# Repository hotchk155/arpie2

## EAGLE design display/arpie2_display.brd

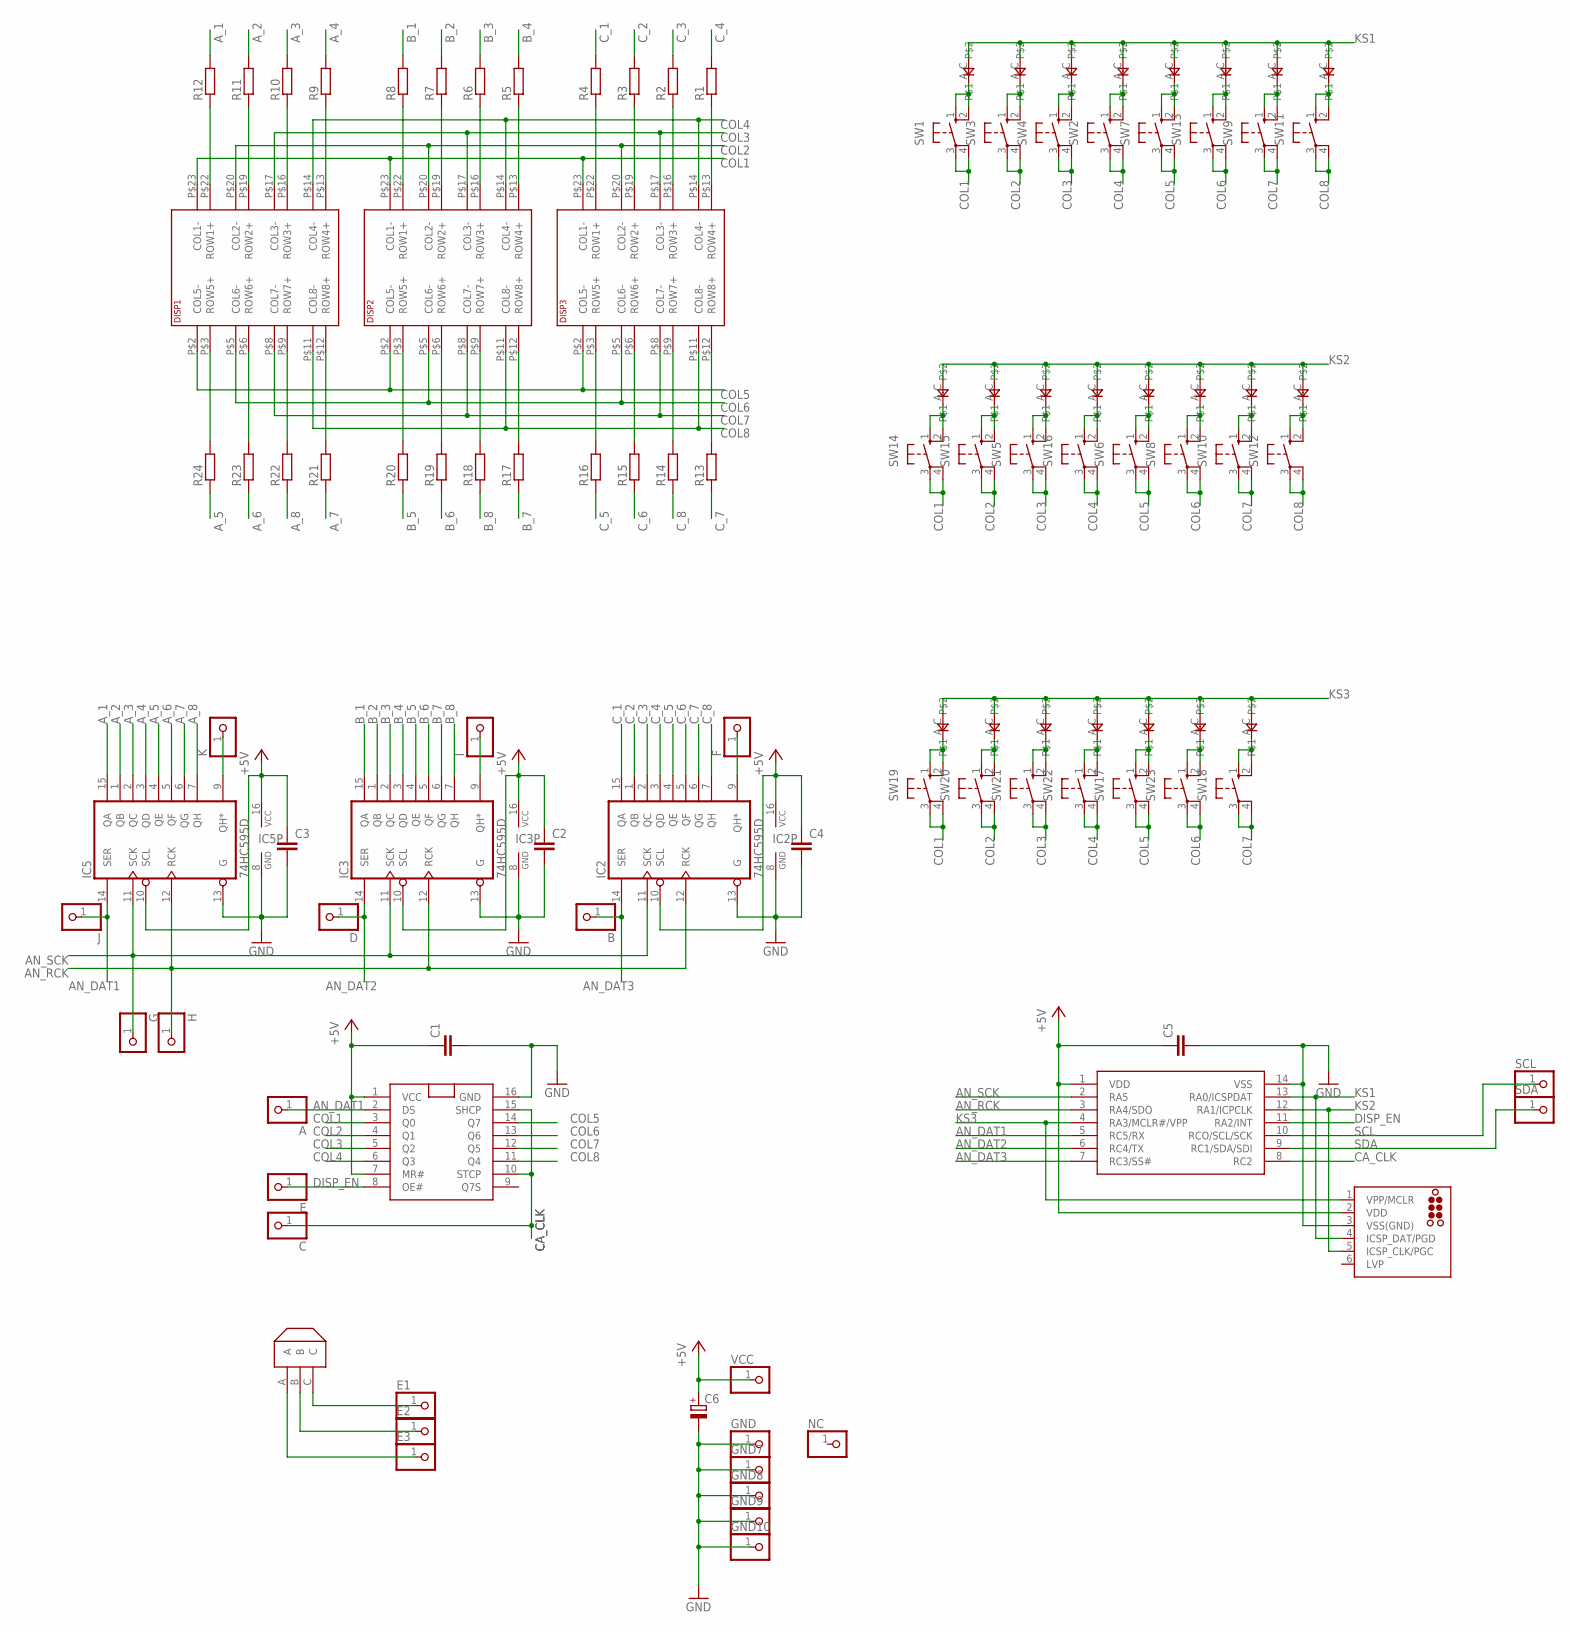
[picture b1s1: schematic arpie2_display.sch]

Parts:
A: PINHD-1X1; 1X01
B: PINHD-1X1; 1X01
C: PINHD-1X1; 1X01
C1, C2, C3, C4, C5: C-EUC0805; C0805
C6: CPOL-EUE2,5-6E; E2,5-6E
D: PINHD-1X1; 1X01
DISP1, DISP2, DISP3: 1388BBMATRIX; 1388LEDMATRIX
E, E1, E2, E3: PINHD-1X1; 1X01
ENC1: ENCODER
F: PINHD-1X1; 1X01
G: PINHD-1X1; 1X01
GND, GND7, GND8, GND9, GND10: PINHD-1X1; 1X01
H: PINHD-1X1; 1X01
I: PINHD-1X1; 1X01
IC1: PIC16F1825SO14; SO14
IC2, IC3, IC5: 74HC595D; SO16
IC4: NPIC6C596; SO16
ICSP: TC2030-MCP-NL
J: PINHD-1X1; 1X01
K: PINHD-1X1; 1X01
NC: PINHD-1X1; 1X01
R1, R2, R3, R4, R5, R6, R7, R8, R9, R10, R11, R12, R13, R14, R15, R16, R17, R18, R19, R20, R21, R22, R23, R24: R-EU_R0805; R0805
SCL: PINHD-1X1; 1X01
SDA: PINHD-1X1; 1X01
SW1, SW2, SW3, SW4, SW5, SW6, SW7, SW8, SW9, SW10, SW11, SW12, SW13, SW14, SW15, SW16, SW17, SW18, SW19, SW20, SW21, SW22, SW23: 10-XX; B3F-10XX
U$2, U$3, U$4, U$5, U$6, U$7, U$8, U$9, U$10, U$11, U$12, U$13, U$14, U$15, U$16, U$17, U$18, U$19, U$20, U$21, U$22, U$23, U$24: 0805DIODE
VCC: PINHD-1X1; 1X01

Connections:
+5V: C1.1, C2.1, C3.1, C4.1, C5.1, C6.+, IC1.1 (VDD), IC2.10 (SCL), IC2.16 (VCC), IC3.10 (SCL), IC3.16 (VCC), IC4.1 (VCC), IC4.7 (MR#), IC5.10 (SCL), IC5.16 (VCC), ICSP.2 (VDD), VCC.1
AN_DAT1: A.1, IC1.5 (RC5/RX), IC4.2 (DS), IC5.14 (SER), J.1
AN_DAT2: D.1, IC1.6 (RC4/TX), IC3.14 (SER)
AN_DAT3: B.1, IC1.7 (RC3/SS#), IC2.14 (SER)
AN_RCK: H.1, IC1.3 (RA4/SDO), IC2.12 (RCK), IC3.12 (RCK), IC5.12 (RCK)
AN_SCK: G.1, IC1.2 (RA5), IC2.11 (SCK), IC3.11 (SCK), IC5.11 (SCK)
A_1: IC5.15 (QA), R12.2
A_2: IC5.1 (QB), R11.2
A_3: IC5.2 (QC), R10.2
A_4: IC5.3 (QD), R9.2
A_5: IC5.4 (QE), R24.1
A_6: IC5.5 (QF), R23.1
A_7: IC5.6 (QG), R21.1
A_8: IC5.7 (QH), R22.1
B_1: IC3.15 (QA), R8.2
B_2: IC3.1 (QB), R7.2
B_3: IC3.2 (QC), R6.2
B_4: IC3.3 (QD), R5.2
B_5: IC3.4 (QE), R20.1
B_6: IC3.5 (QF), R19.1
B_7: IC3.6 (QG), R17.1
B_8: IC3.7 (QH), R18.1
CA_CLK: C.1, IC1.8 (RC2), IC4.10 (STCP), IC4.15 (SHCP)
COL1: DISP1.P$23 (COL1-), DISP2.P$23 (COL1-), DISP3.P$23 (COL1-), IC4.3 (Q0), SW1.3, SW1.4 (P1), SW14.3, SW14.4 (P1), SW19.3, SW19.4 (P1)
COL2: DISP1.P$20 (COL2-), DISP2.P$20 (COL2-), DISP3.P$20 (COL2-), IC4.4 (Q1), SW3.3, SW3.4 (P1), SW15.3, SW15.4 (P1), SW20.3, SW20.4 (P1)
COL3: DISP1.P$17 (COL3-), DISP2.P$17 (COL3-), DISP3.P$17 (COL3-), IC4.5 (Q2), SW4.3, SW4.4 (P1), SW5.3, SW5.4 (P1), SW21.3, SW21.4 (P1)
COL4: DISP1.P$14 (COL4-), DISP2.P$14 (COL4-), DISP3.P$14 (COL4-), IC4.6 (Q3), SW2.3, SW2.4 (P1), SW16.3, SW16.4 (P1), SW22.3, SW22.4 (P1)
COL5: DISP1.P$2 (COL5-), DISP2.P$2 (COL5-), DISP3.P$2 (COL5-), IC4.14 (Q7), SW6.3, SW6.4 (P1), SW7.3, SW7.4 (P1), SW17.3, SW17.4 (P1)
COL6: DISP1.P$5 (COL6-), DISP2.P$5 (COL6-), DISP3.P$5 (COL6-), IC4.13 (Q6), SW8.3, SW8.4 (P1), SW13.3, SW13.4 (P1), SW23.3, SW23.4 (P1)
COL7: DISP1.P$8 (COL7-), DISP2.P$8 (COL7-), DISP3.P$8 (COL7-), IC4.12 (Q5), SW9.3, SW9.4 (P1), SW10.3, SW10.4 (P1), SW18.3, SW18.4 (P1)
COL8: DISP1.P$11 (COL8-), DISP2.P$11 (COL8-), DISP3.P$11 (COL8-), IC4.11 (Q4), SW11.3, SW11.4 (P1), SW12.3, SW12.4 (P1)
C_1: IC2.15 (QA), R4.2
C_2: IC2.1 (QB), R3.2
C_3: IC2.2 (QC), R2.2
C_4: IC2.3 (QD), R1.2
C_5: IC2.4 (QE), R16.1
C_6: IC2.5 (QF), R15.1
C_7: IC2.6 (QG), R13.1
C_8: IC2.7 (QH), R14.1
DISP_EN: E.1, IC1.11 (RA2/INT), IC4.8 (OE#)
GND: C1.2, C2.2, C3.2, C4.2, C5.2, C6.-, GND.1, GND7.1, GND8.1, GND9.1, GND10.1, IC1.14 (VSS), IC2.8 (GND), IC2.13 (G), IC3.8 (GND), IC3.13 (G), IC4.16 (GND), IC5.8 (GND), IC5.13 (G), ICSP.3 (VSS(GND))
KS1: IC1.13 (RA0/ICSPDAT), ICSP.4 (ICSP_DAT/PGD), U$2.C, U$3.C, U$4.C, U$5.C, U$6.C, U$7.C, U$8.C, U$9.C
KS2: IC1.12 (RA1/ICPCLK), ICSP.5 (ICSP_CLK/PGC), U$10.C, U$11.C, U$12.C, U$13.C, U$14.C, U$15.C, U$16.C, U$17.C
KS3: IC1.4 (RA3/MCLR#/VPP), ICSP.1 (VPP/MCLR), U$18.C, U$19.C, U$20.C, U$21.C, U$22.C, U$23.C, U$24.C
unnamed: SW1.1 (S), SW1.2 (S1), U$2.A
unnamed: SW14.1 (S), SW14.2 (S1), U$10.A
unnamed: SW15.1 (S), SW15.2 (S1), U$11.A
unnamed: SW3.1 (S), SW3.2 (S1), U$3.A
unnamed: SW5.1 (S), SW5.2 (S1), U$12.A
unnamed: SW16.1 (S), SW16.2 (S1), U$13.A
unnamed: SW4.1 (S), SW4.2 (S1), U$4.A
unnamed: SW6.1 (S), SW6.2 (S1), U$14.A
unnamed: DISP1.P$22 (ROW1+), R12.1
unnamed: DISP1.P$19 (ROW2+), R11.1
unnamed: DISP1.P$16 (ROW3+), R10.1
unnamed: DISP1.P$13 (ROW4+), R9.1
unnamed: DISP2.P$22 (ROW1+), R8.1
unnamed: DISP2.P$19 (ROW2+), R7.1
unnamed: DISP2.P$16 (ROW3+), R6.1
unnamed: DISP2.P$13 (ROW4+), R5.1
unnamed: DISP3.P$22 (ROW1+), R4.1
unnamed: DISP3.P$19 (ROW2+), R3.1
unnamed: DISP3.P$16 (ROW3+), R2.1
unnamed: DISP3.P$13 (ROW4+), R1.1
unnamed: DISP1.P$3 (ROW5+), R24.2
unnamed: DISP1.P$6 (ROW6+), R23.2
unnamed: DISP1.P$9 (ROW7+), R22.2
unnamed: DISP1.P$12 (ROW8+), R21.2
unnamed: DISP2.P$3 (ROW5+), R20.2
unnamed: DISP2.P$6 (ROW6+), R19.2
unnamed: DISP2.P$9 (ROW7+), R18.2
unnamed: DISP2.P$12 (ROW8+), R17.2
unnamed: DISP3.P$3 (ROW5+), R16.2
unnamed: DISP3.P$6 (ROW6+), R15.2
unnamed: DISP3.P$9 (ROW7+), R14.2
unnamed: DISP3.P$12 (ROW8+), R13.2
unnamed: SW8.1 (S), SW8.2 (S1), U$15.A
unnamed: SW2.1 (S), SW2.2 (S1), U$5.A
unnamed: SW10.1 (S), SW10.2 (S1), U$16.A
unnamed: SW12.1 (S), SW12.2 (S1), U$17.A
unnamed: SW7.1 (S), SW7.2 (S1), U$6.A
unnamed: SW19.1 (S), SW19.2 (S1), U$18.A
unnamed: SW20.1 (S), SW20.2 (S1), U$19.A
unnamed: SW13.1 (S), SW13.2 (S1), U$7.A
unnamed: SW21.1 (S), SW21.2 (S1), U$20.A
unnamed: SW22.1 (S), SW22.2 (S1), U$21.A
unnamed: SW9.1 (S), SW9.2 (S1), U$8.A
unnamed: SW17.1 (S), SW17.2 (S1), U$22.A
unnamed: SW23.1 (S), SW23.2 (S1), U$23.A
unnamed: SW11.1 (S), SW11.2 (S1), U$9.A
unnamed: SW18.1 (S), SW18.2 (S1), U$24.A
unnamed: E1.1, ENC1.C
unnamed: E2.1, ENC1.B
unnamed: E3.1, ENC1.A
unnamed: IC5.9 (QH*), K.1
unnamed: I.1, IC3.9 (QH*)
unnamed: F.1, IC2.9 (QH*)
SCL: IC1.10 (RCO/SCL/SCK), SCL.1
SDA: IC1.9 (RC1/SDA/SDI), SDA.1

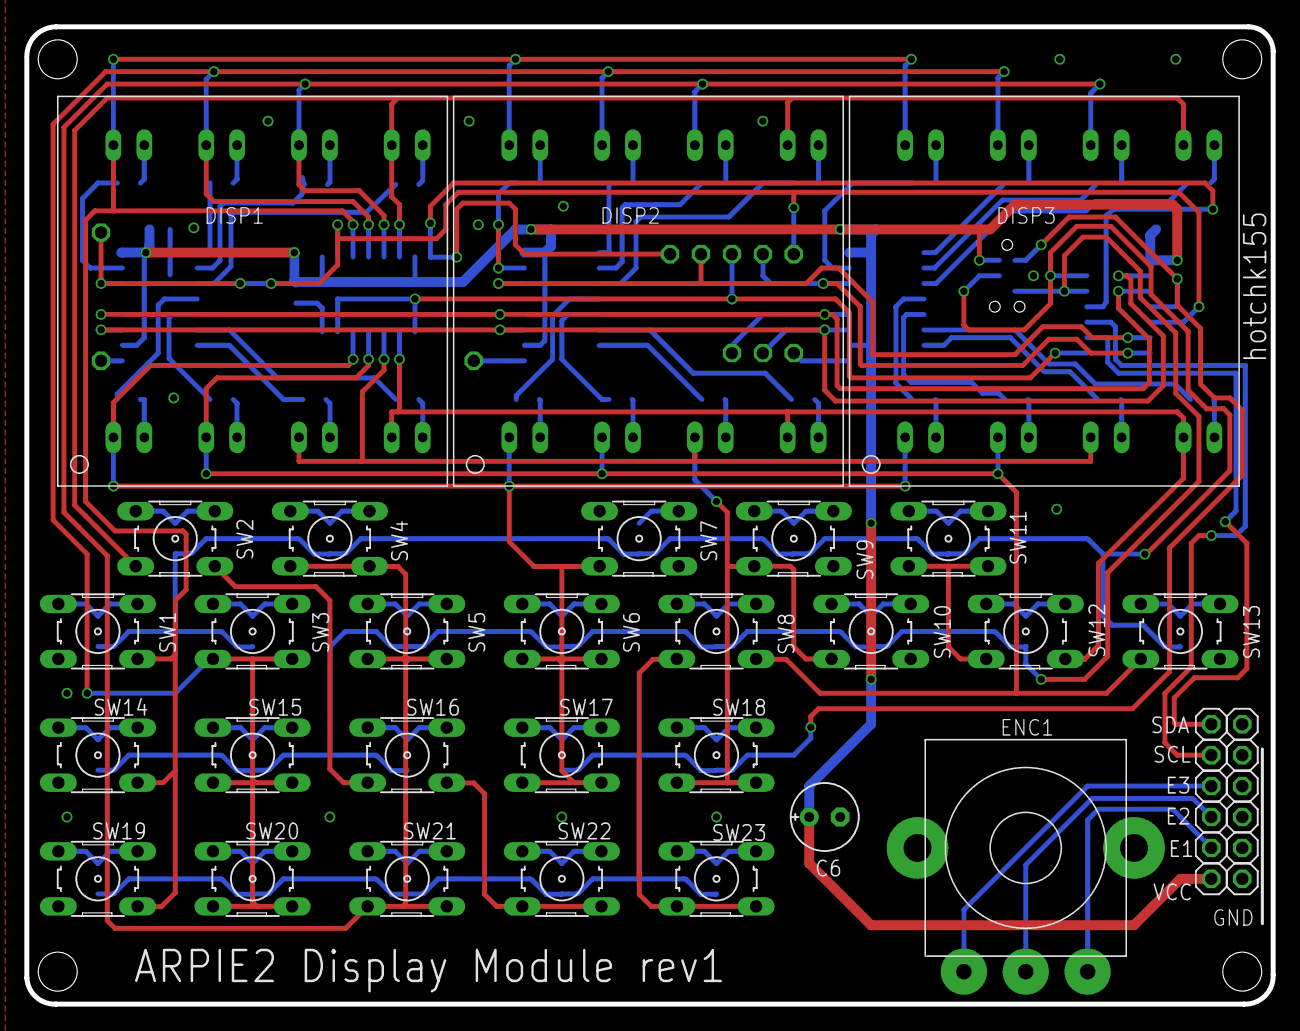
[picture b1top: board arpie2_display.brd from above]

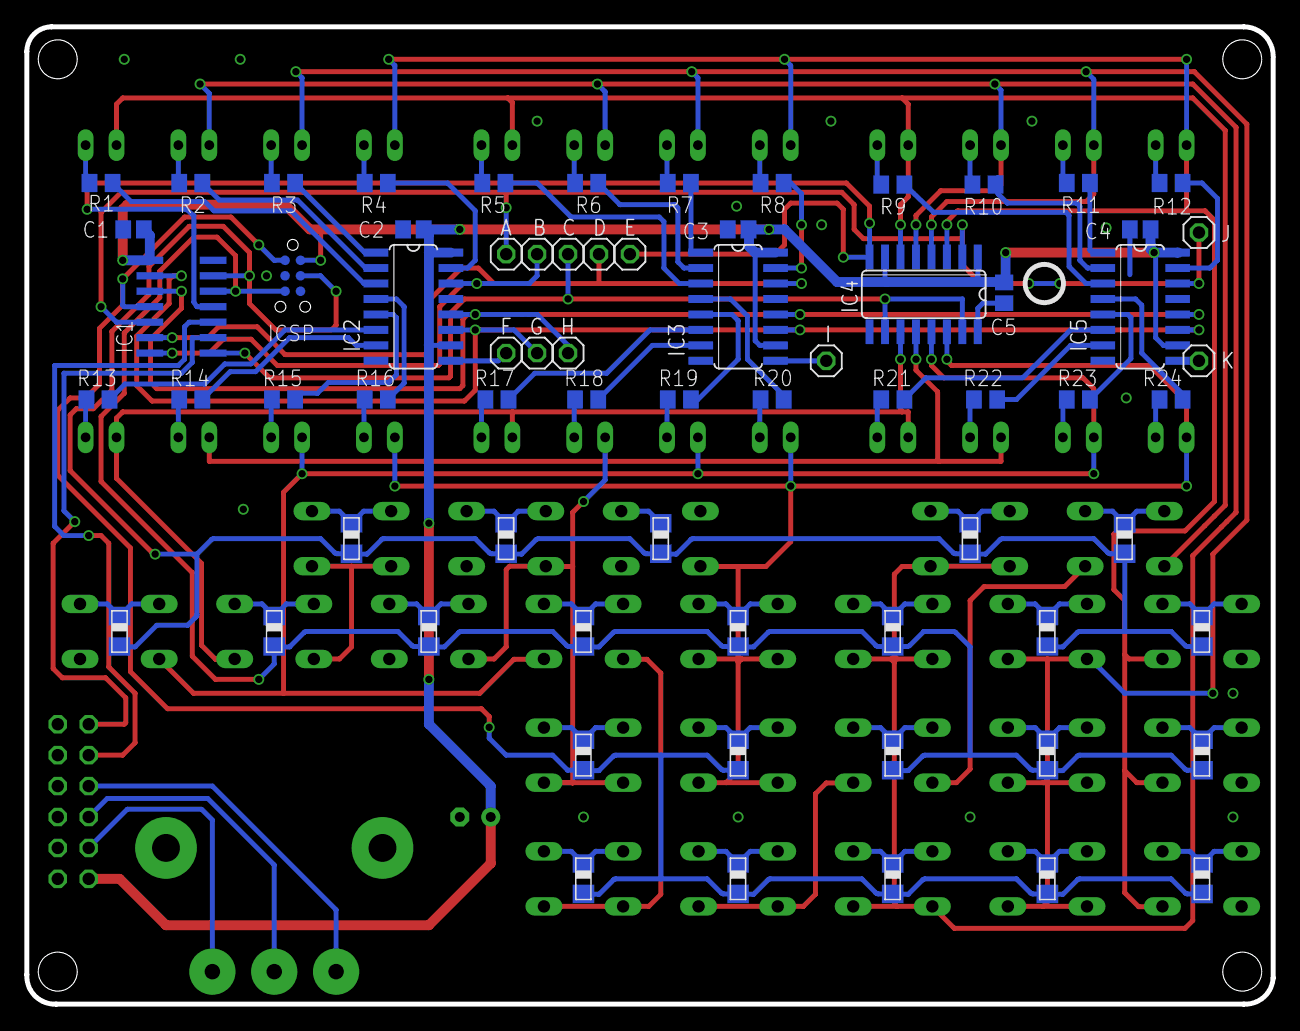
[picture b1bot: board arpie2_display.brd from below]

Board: 2 copper layers, 102.4 x 80.3 mm, 109 parts (69 on the bottom side), 99 nets.

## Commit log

2016-12-05 :neckbeard: Added .gitattributes & .gitignore files
2016-12-26 stuff
2017-01-03 in progress

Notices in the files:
parts and their libraries:
tag-connect: ©2009 ROFA.cz - modified and updated by Robert Darlington ‹rdarlington@gmail.com›
